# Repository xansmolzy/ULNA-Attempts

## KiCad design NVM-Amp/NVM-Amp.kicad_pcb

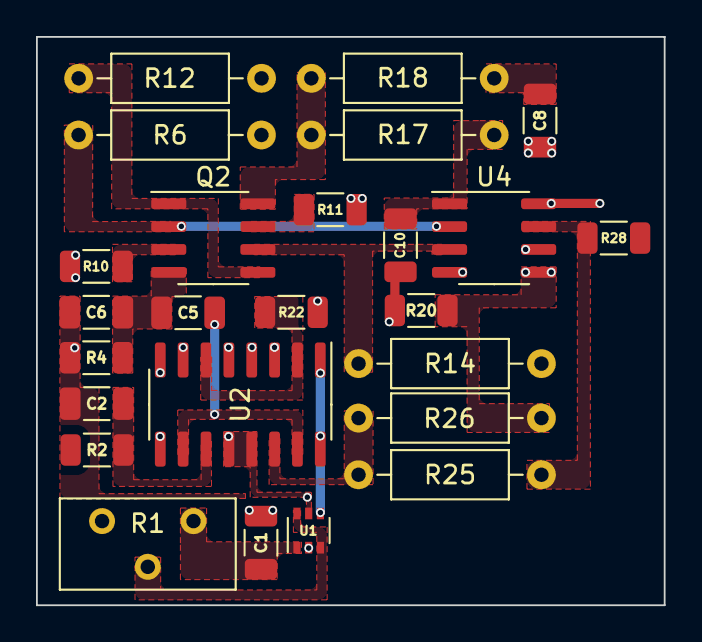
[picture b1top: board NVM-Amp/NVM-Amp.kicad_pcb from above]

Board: 2 copper layers, 34.9 x 31.6 mm, 25 parts (0 on the bottom side), 22 nets.

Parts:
C1, C2, C6: .47uF; C_1206_3216Metric
C5, C8, C10: 1uF; C_1206_3216Metric
Q2: JFE2140; SOIC-8_3.9x4.9mm_P1.27mm
R1: R_Trim; Potentiometer_Bourns_3296Y_Vertical
R2: 3K; R_1206_3216Metric
R4: 100K; R_1206_3216Metric
R6, R14: 909; R_Axial_DIN0207_L6.3mm_D2.5mm_P10.16mm_Horizontal
R10, R11, R28: 100; R_1206_3216Metric
R12: 499; R_Axial_DIN0207_L6.3mm_D2.5mm_P10.16mm_Horizontal
R17: 5M; R_Axial_DIN0207_L6.3mm_D2.5mm_P10.16mm_Horizontal
R18: 10K; R_Axial_DIN0207_L6.3mm_D2.5mm_P10.16mm_Horizontal
R20: 100k; R_1206_3216Metric
R22: 240k; R_1206_3216Metric
R25: 10k; R_Axial_DIN0207_L6.3mm_D2.5mm_P10.16mm_Horizontal
R26: 10; R_Axial_DIN0207_L6.3mm_D2.5mm_P10.16mm_Horizontal
U1: 74LVC2G14; SOT-363_SC-70-6
U2: DG412xY; SOIC-16_3.9x9.9mm_P1.27mm
U4: ADA4522-2; SOIC-8_3.9x4.9mm_P1.27mm

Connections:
+5V: R6.1, R10.1, R14.1, U1.5 (VCC), U2.12 (VL), U2.13 (V+), U4.8 (V+)
-5V: R11.2, R12.2, U2.4 (V-), U4.4 (V-)
/S1: U1.4, U2.1, U2.16
/S2: R1.2, U1.3, U1.6, U2.8, U2.9
GND: C1.1, C2.1, C6.1, C8.2, R4.2, R20.2, R26.2, U1.2 (GND), U2.5 (GND), U2.7, U4.5 (+)
unnamed: C1.2, R1.1, U1.1
unnamed: C2.2, R2.2, U2.11
unnamed: C5.1, U2.10, U2.15
unnamed: C5.2, C6.2, Q2.4, R4.1
unnamed: C8.1, R18.2
unnamed: C10.1, R17.1, U4.1
unnamed: C10.2, R20.1, U2.3
unnamed: Q2.1, Q2.5, R12.1
unnamed: Q2.2, R6.2, U4.2 (-)
unnamed: Q2.3, R10.2
unnamed: Q2.6, R14.2, U4.3 (+)
unnamed: Q2.7, R11.1
unnamed: Q2.8, R17.2, R18.1
unnamed: R22.1, U2.2, U2.6
unnamed: R22.2, U4.6 (-)
unnamed: R25.1, R28.1, U4.7
unnamed: R25.2, R26.1, U2.14

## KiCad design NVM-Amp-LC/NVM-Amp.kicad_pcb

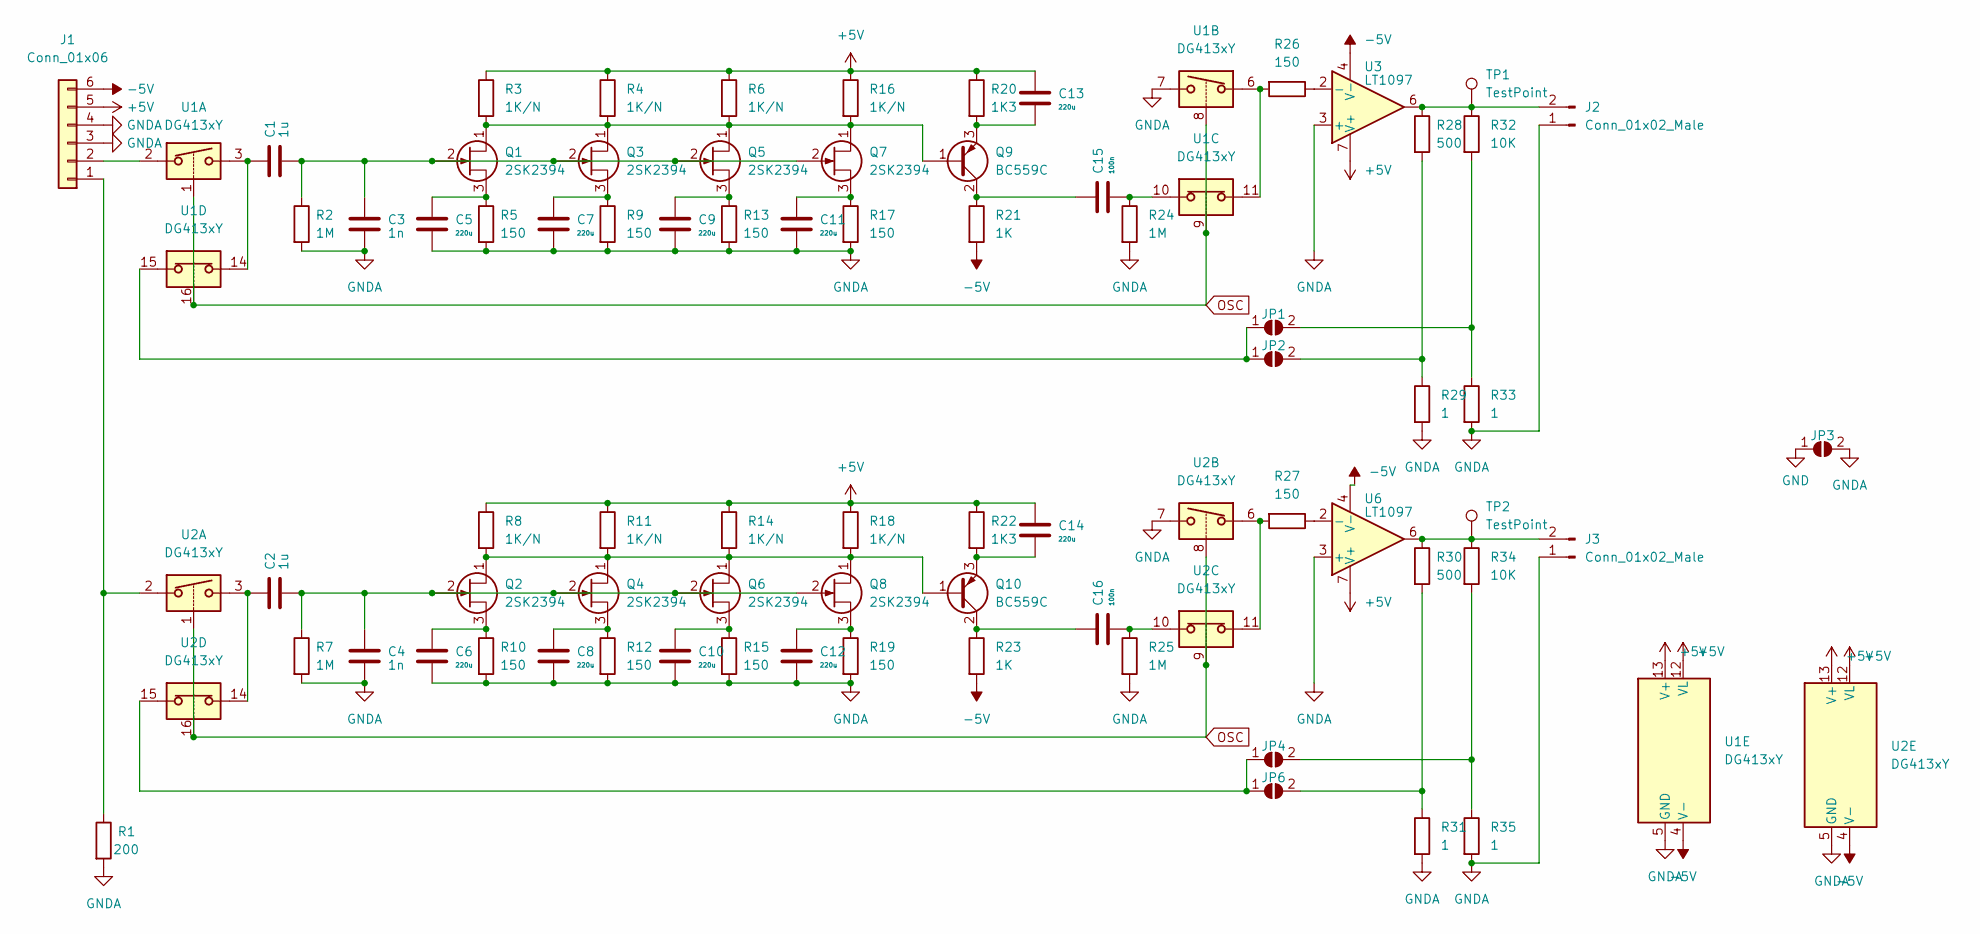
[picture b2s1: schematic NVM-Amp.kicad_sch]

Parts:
C1, C2: 1u; C_1206_3216Metric_Pad1.33x1.80mm_HandSolder
C3, C4: 1n; C_1206_3216Metric_Pad1.33x1.80mm_HandSolder
C5, C6, C7, C8, C9, C10, C11, C12, C13, C14: 220u; C_1206_3216Metric_Pad1.33x1.80mm_HandSolder
C15, C16: 100n; C_1206_3216Metric_Pad1.33x1.80mm_HandSolder
J1: Conn_01x06; PinHeader_1x06_P2.54mm_Vertical
J2, J3: Conn_01x02_Male; PinHeader_1x02_P2.54mm_Vertical
JP1, JP2, JP3, JP4, JP6: SolderJumper_2_Open; SolderJumper-2_P1.3mm_Open_TrianglePad1.0x1.5mm
Q1, Q2, Q3, Q4, Q5, Q6, Q7, Q8: 2SK2394; SOT-23_Handsoldering
Q9, Q10: BC559C; TO-92L_Inline_Wide
R1: 200; C_1206_3216Metric_Pad1.33x1.80mm_HandSolder
R2, R7, R24, R25: 1M; C_1206_3216Metric_Pad1.33x1.80mm_HandSolder
R3, R4, R6, R8, R11, R14, R16, R18: 1K/N; C_1206_3216Metric_Pad1.33x1.80mm_HandSolder
R5, R9, R10, R12, R13, R15, R17, R19, R26, R27: 150; C_1206_3216Metric_Pad1.33x1.80mm_HandSolder
R20, R22: 1K3; C_1206_3216Metric_Pad1.33x1.80mm_HandSolder
R21, R23: 1K; C_1206_3216Metric_Pad1.33x1.80mm_HandSolder
R28, R30: 500; C_1206_3216Metric_Pad1.33x1.80mm_HandSolder
R29, R31, R33, R35: 1; C_1206_3216Metric_Pad1.33x1.80mm_HandSolder
R32, R34: 10K; C_1206_3216Metric_Pad1.33x1.80mm_HandSolder
TP1, TP2: TestPoint; TestPoint_Loop_D2.60mm_Drill1.4mm_Beaded
U1, U2: DG413xY; SOIC-16_3.9x9.9mm_P1.27mm
U3, U6: LT1097; SOIC-8_3.9x4.9mm_P1.27mm

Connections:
+5V: C13.1, C14.1, J1.5, R3.1, R4.1, R6.1, R8.1, R11.1, R14.1, R16.1, R18.1, R20.1, R22.1, U1.12 (VL), U1.13 (V+), U2.12 (VL), U2.13 (V+), U3.7 (V+), U6.7 (V+)
-5V: J1.6, R21.2, R23.2, U1.4 (V-), U2.4 (V-), U3.4 (V-), U6.4 (V-)
GND: JP3.1 (A); also elsewhere on the board
GNDA: C3.2, C4.2, C5.2, C6.2, C7.2, C8.2, C9.2, C10.2, C11.2, C12.2, J1.3, J1.4, J2.1, J3.1, JP3.2 (B), R1.2, R2.2, R5.2, R7.2, R9.2, R10.2, R12.2, R13.2, R15.2, R17.2, R19.2, R24.2, R25.2, R29.2, R31.2, R33.2, R35.2, U1.5 (GND), U1.7, U2.5 (GND), U2.7, U3.3 (+), U6.3 (+); also elsewhere on the board
unnamed: C1.1, U1.3, U1.14
unnamed: C1.2, C3.1, Q1.2 (G), Q3.2 (G), Q5.2 (G), Q7.2 (G), R2.1
unnamed: C2.1, U2.3, U2.14
unnamed: C2.2, C4.1, Q2.2 (G), Q4.2 (G), Q6.2 (G), Q8.2 (G), R7.1
unnamed: C5.1, Q1.3 (S), R5.1
unnamed: C6.1, Q2.3 (S), R10.1
unnamed: C7.1, Q3.3 (S), R9.1
unnamed: C8.1, Q4.3 (S), R12.1
unnamed: C9.1, Q5.3 (S), R13.1
unnamed: C10.1, Q6.3 (S), R15.1
unnamed: C11.1, Q7.3 (S), R17.1
unnamed: C12.1, Q8.3 (S), R19.1
unnamed: C13.2, Q9.3 (E), R20.2
unnamed: C14.2, Q10.3 (E), R22.2
unnamed: C15.1, Q9.2 (C), R21.1
unnamed: C15.2, R24.1, U1.10
unnamed: C16.1, Q10.2 (C), R23.1
unnamed: C16.2, R25.1, U2.10
unnamed: JP1.1 (A), JP2.1 (A), U1.15
unnamed: JP1.2 (B), R32.2, R33.1
unnamed: JP2.2 (B), R28.2, R29.1
unnamed: JP4.1 (A), JP6.1 (A), U2.15
unnamed: JP4.2 (B), R34.2, R35.1
unnamed: JP6.2 (B), R30.2, R31.1
unnamed: Q1.1 (D), Q3.1 (D), Q5.1 (D), Q7.1 (D), Q9.1 (B), R3.2, R4.2, R6.2, R16.2
unnamed: Q2.1 (D), Q4.1 (D), Q6.1 (D), Q8.1 (D), Q10.1 (B), R8.2, R11.2, R14.2, R18.2
unnamed: J1.1, R1.1, U2.2
unnamed: R26.1, U3.2 (-)
unnamed: R26.2, U1.6, U1.11
unnamed: R27.1, U6.2 (-)
unnamed: R27.2, U2.6, U2.11
unnamed: J2.2, R28.1, R32.1, TP1.1, U3.6
unnamed: J3.2, R30.1, R34.1, TP2.1, U6.6
unnamed: J1.2, U1.2
OSC: U1.1, U1.8, U1.9, U1.16, U2.1, U2.8, U2.9, U2.16

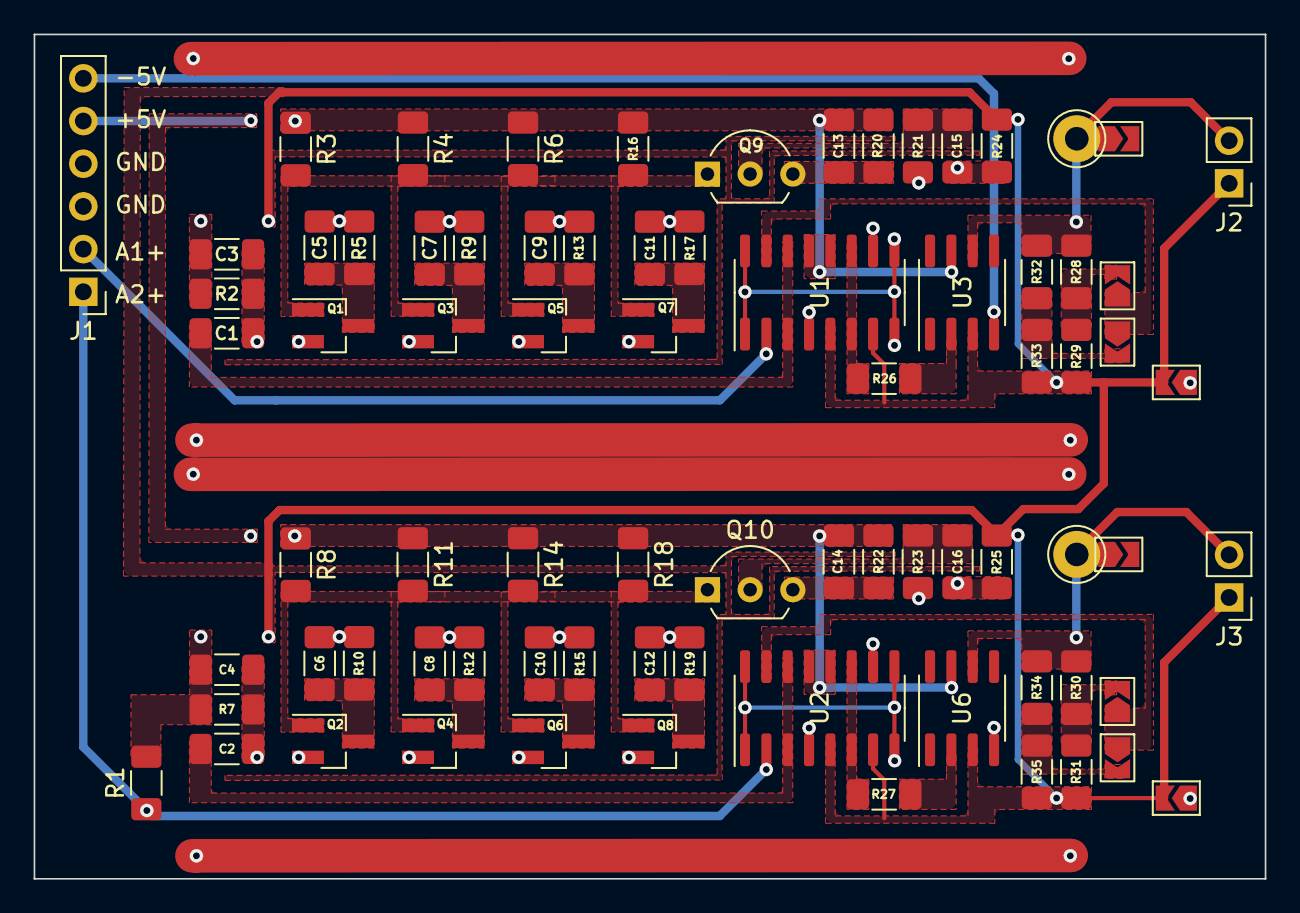
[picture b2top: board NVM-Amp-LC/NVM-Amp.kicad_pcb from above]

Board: 2 copper layers, 73.3 x 50.2 mm, 78 parts (0 on the bottom side), 39 nets.

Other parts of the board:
JP3#2, JP5, JP7: SolderJumper_2_Open; SolderJumper-2_P1.3mm_Open_TrianglePad1.0x1.5mm

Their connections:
GND: JP3#2.1 (A); also elsewhere on the board
GNDA: JP3#2.2 (B); also elsewhere on the board

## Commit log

2022-11-11 Add two attempts
